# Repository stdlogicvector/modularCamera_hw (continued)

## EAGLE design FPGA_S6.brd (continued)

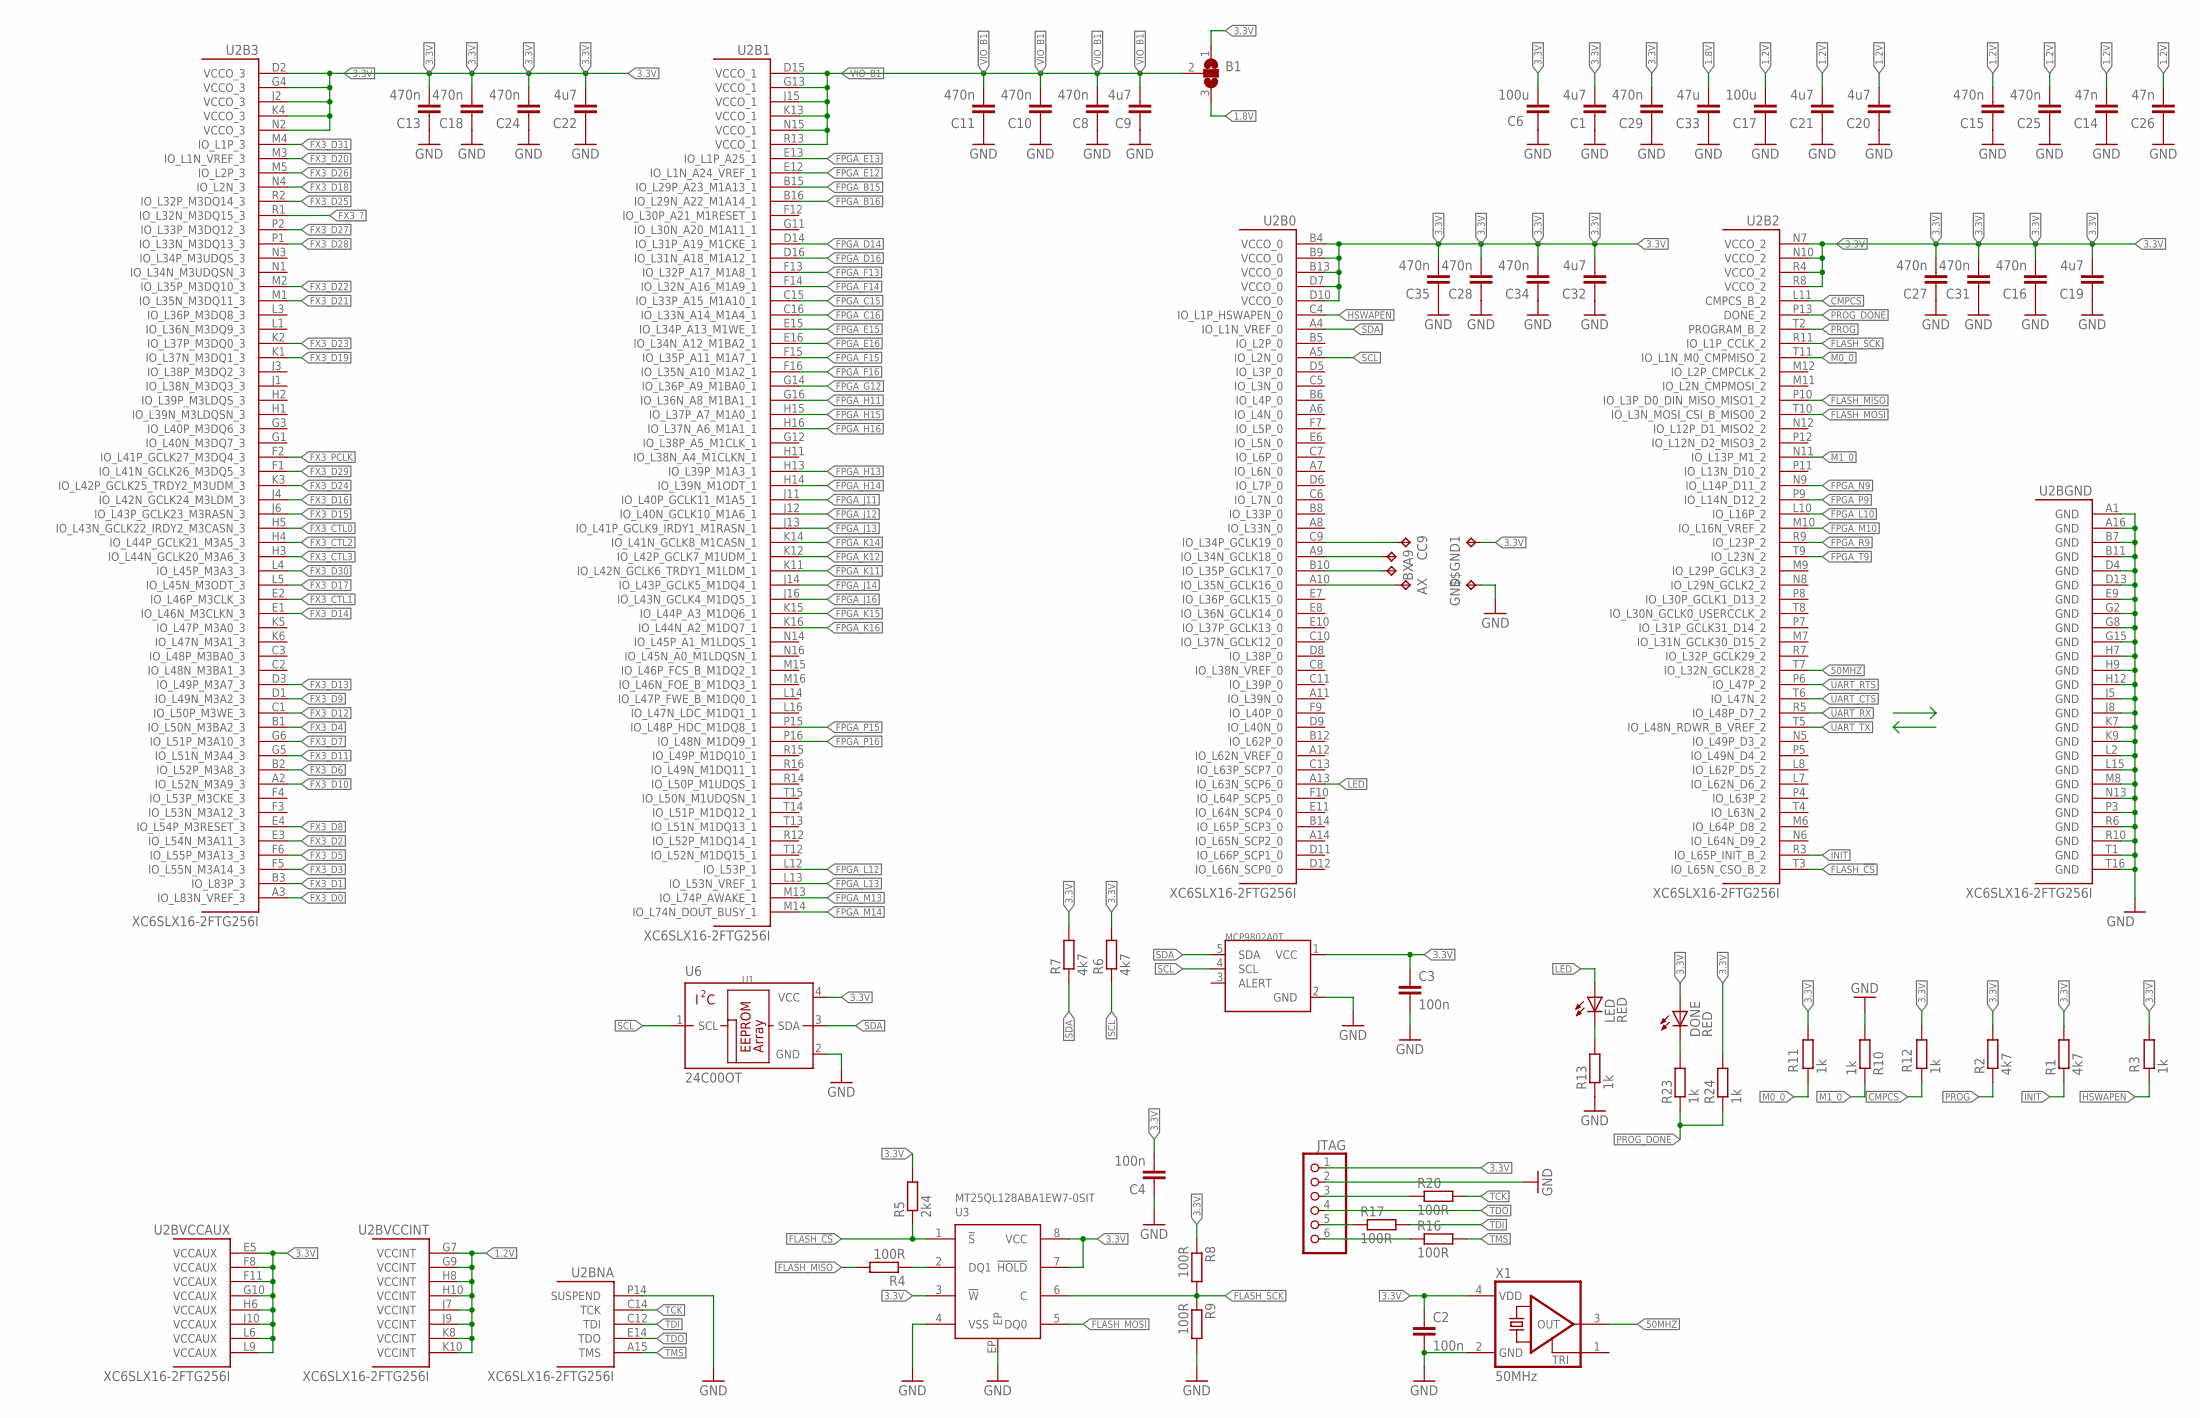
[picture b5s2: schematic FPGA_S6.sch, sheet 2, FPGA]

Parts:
$$GND1: TPTP15R; TP15R
A9: TPTP15R; TP15R
AX: TPTP15R; TP15R
B1: SJ2W; SJ_2
BX: TPTP15R; TP15R
C1, C9, C19, C20, C21, C22, C32: 4u7; C0603; LCSC C19666
C2, C3, C4: 100n; C0402; LCSC C1525
C6, C17: 100u; C1206; DIGIKEY 490-GRM31CD80J107MEA8LCT-ND
C8, C10, C11, C13, C15, C16, C18, C24, C25, C27, C28, C29, C31, C34, C35: 470n; C0402; LCSC C162159
C14, C26: 47n; C0402; LCSC C327054
C33: 47u; C0805; LCSC C77072
CC9: TPTP15R; TP15R
DONE: RED; CHIP-LED0603; LCSC C7493803
GND: TPTP15R; TP15R
JTAG: PINHD-1X6_2.00; 1X06M
LED: RED; CHIP-LED0603; LCSC C7493803
R1, R2, R6, R7: 4k7; R0402; LCSC C25900
R3, R10, R11, R12, R13, R23, R24: 1k; R0402; LCSC C11702
R4, R8, R9, R16, R17, R20: 100R; R0402; LCSC C25076
R5: 2k4; R0402
U1: MCP9802A0T; SOT23-5L; FARNELL 1439487
U2: XC6SLX16-2FTG256I; FT256; DIGIKEY 122-1752-ND
U3: MT25QL128ABA1EW7-0SIT
U6: 24C00OT; SOT23-5L
X1: 50MHz; ASE; MPN_ ASE-50.000MHZ-E-T; FARNELL 2467898

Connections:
1.2V: C14.2, C15.2, C17.1, C20.2, C21.2, C25.2, C26.2, U2.G7 (VCCINT), U2.G9 (VCCINT), U2.H8 (VCCINT), U2.H10 (VCCINT), U2.J7 (VCCINT), U2.J9 (VCCINT), U2.K8 (VCCINT), U2.K10 (VCCINT); also elsewhere on the board
1.8V: B1.3, C33.2; also elsewhere on the board
3.3V: $$GND1.TP, B1.1, C1.2, C2.1, C3.1, C4.2, C6.1, C13.2, C16.2, C18.2, C19.2, C22.2, C24.2, C27.2, C28.2, C29.2, C31.2, C32.2, C34.2, C35.2, DONE.A, JTAG.1, R1.2, R2.1, R3.1, R5.2, R6.1, R7.1, R8.1, R11.1, R12.1, R24.2, U1.1 (VCC), U2.B4 (VCCO_0), U2.B9 (VCCO_0), U2.B13 (VCCO_0), U2.D2 (VCCO_3), U2.D7 (VCCO_0), U2.D10 (VCCO_0), U2.E5 (VCCAUX), U2.F8 (VCCAUX), U2.F11 (VCCAUX), U2.G4 (VCCO_3), U2.G10 (VCCAUX), U2.H6 (VCCAUX), U2.J2 (VCCO_3), U2.J10 (VCCAUX), U2.K4 (VCCO_3), U2.L6 (VCCAUX), U2.L9 (VCCAUX), U2.N2 (VCCO_3), U2.N7 (VCCO_2), U2.N10 (VCCO_2), U2.R4 (VCCO_2), U2.R8 (VCCO_2), U3.3 (!W), U3.7 (!HOLD), U3.8 (VCC), U6.4 (VCC), X1.4 (VDD); also elsewhere on the board
50MHZ: U2.T7 (IO_L32N_GCLK28_2), X1.3 (OUT)
CMPCS: R12.2, U2.L11 (CMPCS_B_2)
FLASH_!CS: R5.1, U2.T3 (IO_L65N_CSO_B_2), U3.1 (!S)
FLASH_MISO: R4.2, U2.P10 (IO_L3P_D0_DIN_MISO_MISO1_2)
FLASH_MOSI: U2.T10 (IO_L3N_MOSI_CSI_B_MISO0_2), U3.5 (DQ0)
FLASH_SCK: R8.2, R9.1, U2.R11 (IO_L1P_CCLK_2), U3.6 (C)
FPGA_B15: U2.B15 (IO_L29P_A23_M1A13_1); also elsewhere on the board
FPGA_B16: U2.B16 (IO_L29N_A22_M1A14_1); also elsewhere on the board
FPGA_C15: U2.C15 (IO_L33P_A15_M1A10_1); also elsewhere on the board
FPGA_C16: U2.C16 (IO_L33N_A14_M1A4_1); also elsewhere on the board
FPGA_D14: U2.D14 (IO_L31P_A19_M1CKE_1); also elsewhere on the board
FPGA_D16: U2.D16 (IO_L31N_A18_M1A12_1); also elsewhere on the board
FPGA_E12: U2.E12 (IO_L1N_A24_VREF_1); also elsewhere on the board
FPGA_E13: U2.E13 (IO_L1P_A25_1); also elsewhere on the board
FPGA_E15: U2.E15 (IO_L34P_A13_M1WE_1); also elsewhere on the board
FPGA_E16: U2.E16 (IO_L34N_A12_M1BA2_1); also elsewhere on the board
FPGA_F13: U2.F13 (IO_L32P_A17_M1A8_1); also elsewhere on the board
FPGA_F14: U2.F14 (IO_L32N_A16_M1A9_1); also elsewhere on the board
FPGA_F15: U2.F15 (IO_L35P_A11_M1A7_1); also elsewhere on the board
FPGA_F16: U2.F16 (IO_L35N_A10_M1A2_1); also elsewhere on the board
FPGA_G12: U2.G14 (IO_L36P_A9_M1BA0_1); also elsewhere on the board
FPGA_H11: U2.G16 (IO_L36N_A8_M1BA1_1); also elsewhere on the board
FPGA_H13: U2.H13 (IO_L39P_M1A3_1); also elsewhere on the board
FPGA_H14: U2.H14 (IO_L39N_M1ODT_1); also elsewhere on the board
FPGA_H15: U2.H15 (IO_L37P_A7_M1A0_1); also elsewhere on the board
FPGA_H16: U2.H16 (IO_L37N_A6_M1A1_1); also elsewhere on the board
FPGA_J11: U2.J11 (IO_L40P_GCLK11_M1A5_1); also elsewhere on the board
FPGA_J12: U2.J12 (IO_L40N_GCLK10_M1A6_1); also elsewhere on the board
FPGA_J13: U2.J13 (IO_L41P_GCLK9_IRDY1_M1RASN_1); also elsewhere on the board
FPGA_J14: U2.J14 (IO_L43P_GCLK5_M1DQ4_1); also elsewhere on the board
FPGA_J16: U2.J16 (IO_L43N_GCLK4_M1DQ5_1); also elsewhere on the board
FPGA_K11: U2.K11 (IO_L42N_GCLK6_TRDY1_M1LDM_1); also elsewhere on the board
FPGA_K12: U2.K12 (IO_L42P_GCLK7_M1UDM_1); also elsewhere on the board
FPGA_K14: U2.K14 (IO_L41N_GCLK8_M1CASN_1); also elsewhere on the board
FPGA_K15: U2.K15 (IO_L44P_A3_M1DQ6_1); also elsewhere on the board
FPGA_K16: U2.K16 (IO_L44N_A2_M1DQ7_1); also elsewhere on the board
FPGA_L10: U2.L10 (IO_L16P_2); also elsewhere on the board
FPGA_L12: U2.L12 (IO_L53P_1); also elsewhere on the board
FPGA_L13: U2.L13 (IO_L53N_VREF_1); also elsewhere on the board
FPGA_M10: U2.M10 (IO_L16N_VREF_2); also elsewhere on the board
FPGA_M13: U2.M13 (IO_L74P_AWAKE_1); also elsewhere on the board
FPGA_M14: U2.M14 (IO_L74N_DOUT_BUSY_1); also elsewhere on the board
FPGA_N9: U2.N9 (IO_L14P_D11_2); also elsewhere on the board
FPGA_P9: U2.P9 (IO_L14N_D12_2); also elsewhere on the board
FPGA_P15: U2.P15 (IO_L48P_HDC_M1DQ8_1); also elsewhere on the board
FPGA_P16: U2.P16 (IO_L48N_M1DQ9_1); also elsewhere on the board
FPGA_R9: U2.R9 (IO_L23P_2); also elsewhere on the board
FPGA_T9: U2.T9 (IO_L23N_2); also elsewhere on the board
FX3_?: U2.R1 (IO_L32N_M3DQ15_3); also elsewhere on the board
FX3_CTL0: U2.H5 (IO_L43N_GCLK22_IRDY2_M3CASN_3); also elsewhere on the board
FX3_CTL1: U2.E2 (IO_L46P_M3CLK_3); also elsewhere on the board
FX3_CTL2: U2.H4 (IO_L44P_GCLK21_M3A5_3); also elsewhere on the board
FX3_CTL3: U2.H3 (IO_L44N_GCLK20_M3A6_3); also elsewhere on the board
FX3_D0: U2.A3 (IO_L83N_VREF_3); also elsewhere on the board
FX3_D1: U2.B3 (IO_L83P_3); also elsewhere on the board
FX3_D2: U2.E3 (IO_L54N_M3A11_3); also elsewhere on the board
FX3_D3: U2.F5 (IO_L55N_M3A14_3); also elsewhere on the board
FX3_D4: U2.B1 (IO_L50N_M3BA2_3); also elsewhere on the board
FX3_D5: U2.F6 (IO_L55P_M3A13_3); also elsewhere on the board
FX3_D6: U2.B2 (IO_L52P_M3A8_3); also elsewhere on the board
FX3_D7: U2.G6 (IO_L51P_M3A10_3); also elsewhere on the board
FX3_D8: U2.E4 (IO_L54P_M3RESET_3); also elsewhere on the board
FX3_D9: U2.D1 (IO_L49N_M3A2_3); also elsewhere on the board
FX3_D10: U2.A2 (IO_L52N_M3A9_3); also elsewhere on the board
FX3_D11: U2.G5 (IO_L51N_M3A4_3); also elsewhere on the board
FX3_D12: U2.C1 (IO_L50P_M3WE_3); also elsewhere on the board
FX3_D13: U2.D3 (IO_L49P_M3A7_3); also elsewhere on the board
FX3_D14: U2.E1 (IO_L46N_M3CLKN_3); also elsewhere on the board
FX3_D15: U2.J6 (IO_L43P_GCLK23_M3RASN_3); also elsewhere on the board
FX3_D16: U2.J4 (IO_L42N_GCLK24_M3LDM_3); also elsewhere on the board
FX3_D17: U2.L5 (IO_L45N_M3ODT_3); also elsewhere on the board
FX3_D18: U2.N4 (IO_L2N_3); also elsewhere on the board
FX3_D19: U2.K1 (IO_L37N_M3DQ1_3); also elsewhere on the board
FX3_D20: U2.M3 (IO_L1N_VREF_3); also elsewhere on the board
FX3_D21: U2.M1 (IO_L35N_M3DQ11_3); also elsewhere on the board
FX3_D22: U2.M2 (IO_L35P_M3DQ10_3); also elsewhere on the board
FX3_D23: U2.K2 (IO_L37P_M3DQ0_3); also elsewhere on the board
FX3_D24: U2.K3 (IO_L42P_GCLK25_TRDY2_M3UDM_3); also elsewhere on the board
FX3_D25: U2.R2 (IO_L32P_M3DQ14_3); also elsewhere on the board
FX3_D26: U2.M5 (IO_L2P_3); also elsewhere on the board
FX3_D27: U2.P2 (IO_L33P_M3DQ12_3); also elsewhere on the board
FX3_D28: U2.P1 (IO_L33N_M3DQ13_3); also elsewhere on the board
FX3_D29: U2.F1 (IO_L41N_GCLK26_M3DQ5_3); also elsewhere on the board
FX3_D30: U2.L4 (IO_L45P_M3A3_3); also elsewhere on the board
FX3_D31: U2.M4 (IO_L1P_3); also elsewhere on the board
FX3_PCLK: U2.F2 (IO_L41P_GCLK27_M3DQ4_3); also elsewhere on the board
GND: C1.1, C2.2, C3.2, C4.1, C6.2, C8.1, C9.1, C10.1, C11.1, C13.1, C14.1, C15.1, C16.1, C17.2, C18.1, C19.1, C20.1, C21.1, C22.1, C24.1, C25.1, C26.1, C27.1, C28.1, C29.1, C31.1, C32.1, C33.1, C34.1, C35.1, GND.TP, JTAG.2, R9.2, R10.2, R13.1, U1.2 (GND), U2.A1 (GND), U2.A16 (GND), U2.B7 (GND), U2.B11 (GND), U2.D4 (GND), U2.D13 (GND), U2.E9 (GND), U2.G2 (GND), U2.G8 (GND), U2.G15 (GND), U2.H7 (GND), U2.H9 (GND), U2.H12 (GND), U2.J5 (GND), U2.J8 (GND), U2.K7 (GND), U2.K9 (GND), U2.L2 (GND), U2.L15 (GND), U2.M8 (GND), U2.N13 (GND), U2.P3 (GND), U2.P14 (SUSPEND), U2.R6 (GND), U2.R10 (GND), U2.T1 (GND), U2.T16 (GND), U3.4 (VSS), U3.EP, U6.2 (GND), X1.2 (GND); also elsewhere on the board
HSWAPEN: R3.2, U2.C4 (IO_L1P_HSWAPEN_0)
INIT: R1.1, U2.R3 (IO_L65P_INIT_B_2)
LED: LED.A, U2.A13 (IO_L63N_SCP6_0)
M0_0: R11.2, U2.T11 (IO_L1N_M0_CMPMISO_2)
M1_0: R10.1, U2.N11 (IO_L13P_M1_2)
unnamed: BX.TP, U2.B10 (IO_L35P_GCLK17_0)
unnamed: LED.C, R13.2
unnamed: R4.1, U3.2 (DQ1)
unnamed: AX.TP, U2.A10 (IO_L35N_GCLK16_0)
unnamed: A9.TP, U2.A9 (IO_L34N_GCLK18_0)
unnamed: CC9.TP, U2.C9 (IO_L34P_GCLK19_0)
unnamed: DONE.C, R23.2
unnamed: JTAG.5, R17.1
unnamed: JTAG.3, R20.1
unnamed: JTAG.6, R16.1
PROG: R2.2, U2.T2 (PROGRAM_B_2)
PROG_DONE: R23.1, R24.1, U2.P13 (DONE_2)
SCL: R6.2, U1.4 (SCL), U2.A5 (IO_L2N_0), U6.1 (SCL)
SDA: R7.2, U1.5 (SDA), U2.A4 (IO_L1N_VREF_0), U6.3 (SDA)
TCK: R20.2, U2.C14 (TCK)
TDI: R17.2, U2.C12 (TDI)
TDO: JTAG.4, U2.E14 (TDO)
TMS: R16.2, U2.A15 (TMS)
UART_CTS: U2.T6 (IO_L47N_2); also elsewhere on the board
UART_RTS: U2.P6 (IO_L47P_2); also elsewhere on the board
UART_RX: U2.R5 (IO_L48P_D7_2); also elsewhere on the board
UART_TX: U2.T5 (IO_L48N_RDWR_B_VREF_2); also elsewhere on the board
VIO_B1: B1.2, C8.2, C9.2, C10.2, C11.2, U2.D15 (VCCO_1), U2.G13 (VCCO_1), U2.J15 (VCCO_1), U2.K13 (VCCO_1), U2.N15 (VCCO_1), U2.R13 (VCCO_1)

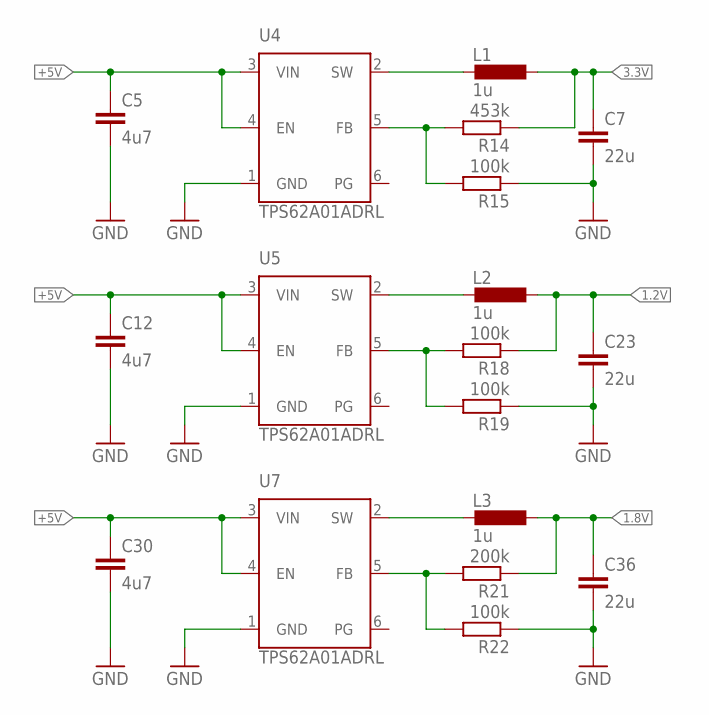
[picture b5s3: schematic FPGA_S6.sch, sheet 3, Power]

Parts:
C5, C12, C30: 4u7; C0603; LCSC C19666
C7, C23, C36: 22u; C0603; LCSC C109448
L1, L2, L3: 1u; L1008; MPN LQM2HPN1R0MG0L; DIGIKEY 490-5112-1-ND
R14: 453k; R0402; LCSC C137978
R15: 100k; R0402; DIGIKEY RMCF0402FT100KCT-ND
R18: 100k; R0402; DIGIKEY RMCF0402FT66K5CT-ND
R19, R22: 100k; R0402; LCSC C60491
R21: 200k; R0402; LCSC C114763
U4, U5, U7: TPS62A01ADRL; SOTFL50P160X60-6N; DIGIKEY 296-TPS62A01ADRLRCT-ND

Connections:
1.2V: C23.1, L2.1, R18.1; also elsewhere on the board
1.8V: C36.1, L3.1, R21.1; also elsewhere on the board
3.3V: C7.1, L1.1, R14.1; also elsewhere on the board
+5V: C5.1, C12.1, C30.1, U4.3 (VIN), U4.4 (EN), U5.3 (VIN), U5.4 (EN), U7.3 (VIN), U7.4 (EN); also elsewhere on the board
GND: C5.2, C7.2, C12.2, C23.2, C30.2, C36.2, R15.1, R19.1, R22.1, U4.1 (GND), U5.1 (GND), U7.1 (GND); also elsewhere on the board
unnamed: L2.2, U5.2 (SW)
unnamed: R18.2, R19.2, U5.5 (FB)
unnamed: R14.2, R15.2, U4.5 (FB)
unnamed: L3.2, U7.2 (SW)
unnamed: R21.2, R22.2, U7.5 (FB)
unnamed: L1.2, U4.2 (SW)

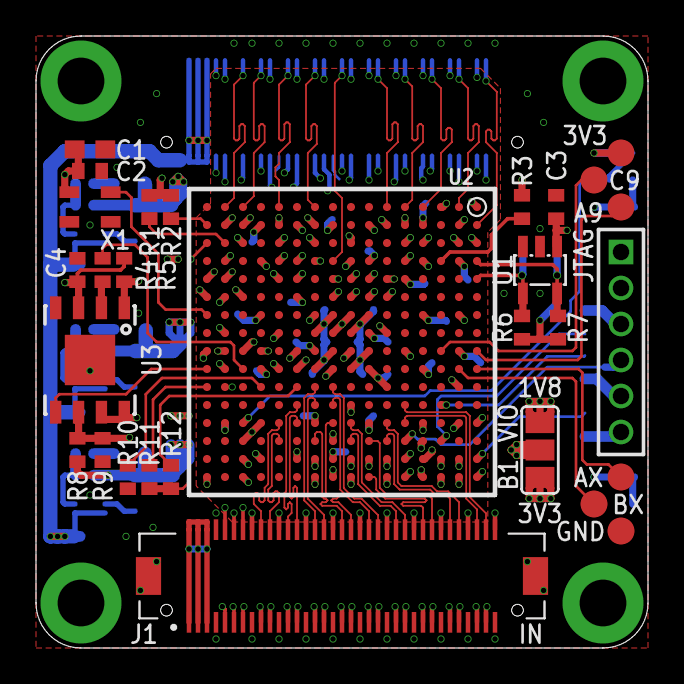
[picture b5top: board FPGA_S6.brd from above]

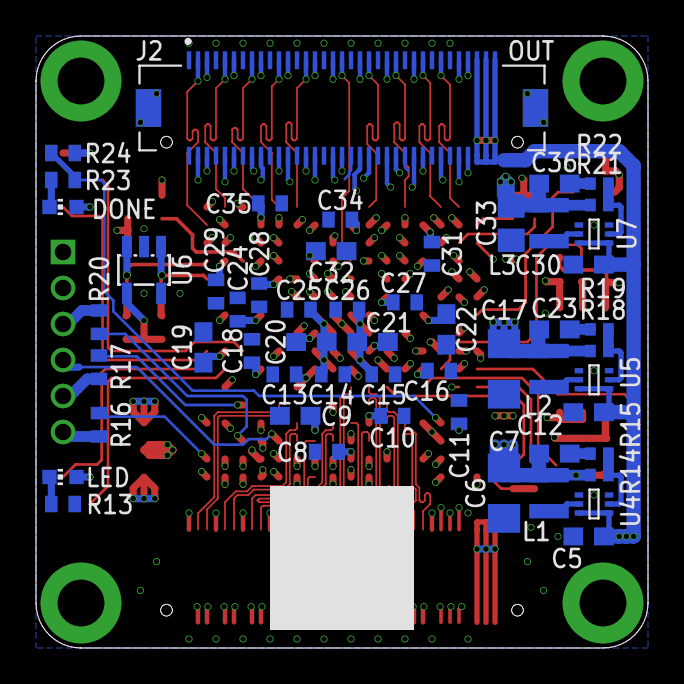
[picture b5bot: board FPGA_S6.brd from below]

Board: 6 copper layers, 34.0 x 34.0 mm, 83 parts (54 on the bottom side), 125 nets.

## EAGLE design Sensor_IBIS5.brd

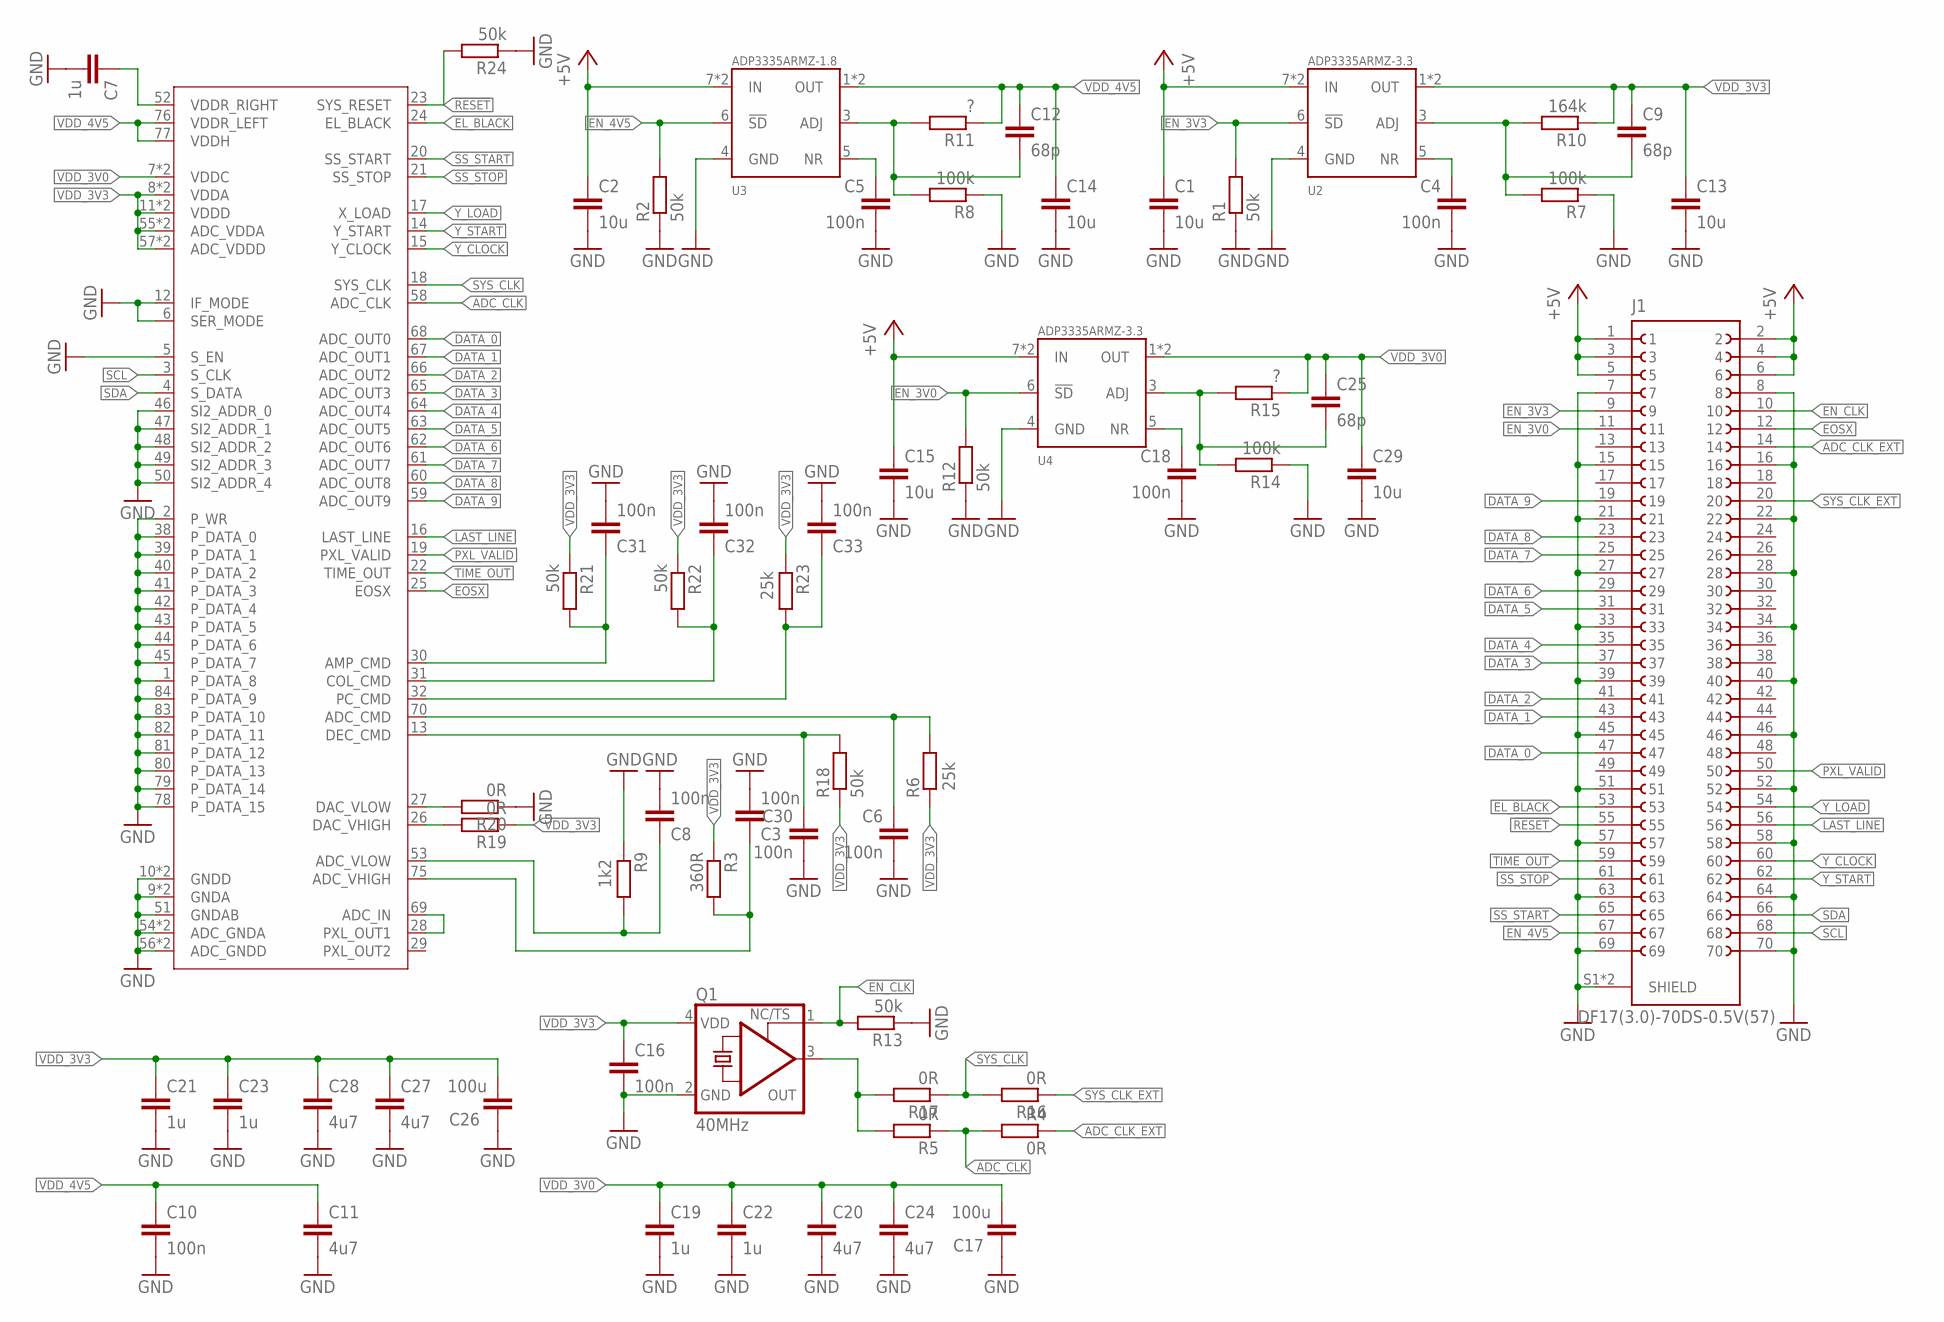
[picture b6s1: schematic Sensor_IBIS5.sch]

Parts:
C1, C2, C13, C14, C15, C29: 10u; C0603
C3, C4, C5, C6, C8, C10, C16, C18, C30, C31, C32, C33: 100n; C0402; LCSC C1525
C7, C19, C21, C22, C23: 1u; C0402
C9, C12, C25: 68p; C0402; LCSC C1525
C11, C20, C24, C27, C28: 4u7; C0603; LCSC C19666
C17, C26: 100u; C1206; DIGIKEY 490-GRM31CD80J107MEA8LCT-ND
J1: DF17(3.0)-70DS-0.5V(57)
Q1: 40MHz; 3.2X2.5_KXO-V96; DIGIKEY 1473-SIT8208AC-23-33E-72.000000-ND
R1, R2, R12, R13, R18, R21, R22, R24: 50k; R0402
R3: 360R; R0402
R4, R5, R16, R17, R19, R20: 0R; R0402
R6, R23: 25k; R0402
R7, R8, R14: 100k; R0402
R9: 1k2; R0402
R10: 164k; R0402
R11, R15: ?; R0402
U1: CYII5FM1300AB; LCC-84
U2, U4: ADP3335ARMZ-3.3; MSOP08; DIGIKEY 505-ADP3335ARMZ-3.3RL7CT-ND
U3: ADP3335ARMZ-1.8; MSOP08; DIGIKEY 505-ADP3335ARMZ-1.8-R7CT-ND

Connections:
!RESET: J1.55, R24.2, U1.23 (SYS_RESET)
+5V: C1.1, C2.1, C15.1, J1.1, J1.2, J1.3, J1.4, J1.5, J1.6, U2.7 (IN), U2.8 (IN), U3.7 (IN), U3.8 (IN), U4.7 (IN), U4.8 (IN)
ADC_CLK: R4.2, R5.1, U1.58 (ADC_CLK)
ADC_CLK_EXT: J1.14, R4.1
CLK: Q1.3 (OUT), R5.2, R17.2
DATA_0: J1.47, U1.68 (ADC_OUT0)
DATA_1: J1.43, U1.67 (ADC_OUT1)
DATA_2: J1.41, U1.66 (ADC_OUT2)
DATA_3: J1.37, U1.65 (ADC_OUT3)
DATA_4: J1.35, U1.64 (ADC_OUT4)
DATA_5: J1.31, U1.63 (ADC_OUT5)
DATA_6: J1.29, U1.62 (ADC_OUT6)
DATA_7: J1.25, U1.61 (ADC_OUT7)
DATA_8: J1.23, U1.60 (ADC_OUT8)
DATA_9: J1.19, U1.59 (ADC_OUT9)
EL_BLACK: J1.53, U1.24 (EL_BLACK)
EN_3V0: J1.11, R12.2, U4.6 (!SD)
EN_3V3: J1.9, R1.2, U2.6 (!SD)
EN_4V5: J1.67, R2.2, U3.6 (!SD)
EN_CLK: J1.10, Q1.1 (TS), R13.2
EOSX: J1.12, U1.25 (EOSX)
GND: C1.2, C2.2, C3.2, C4.2, C5.2, C6.2, C7.2, C8.2, C10.2, C11.2, C13.2, C14.2, C15.2, C16.2, C17.2, C18.2, C19.2, C20.2, C21.2, C22.2, C23.2, C24.2, C26.2, C27.2, C28.2, C29.2, C30.2, C31.2, C32.2, C33.2, J1.7, J1.8, J1.15, J1.16, J1.21, J1.22, J1.27, J1.28, J1.33, J1.34, J1.39, J1.40, J1.45, J1.46, J1.51, J1.52, J1.57, J1.58, J1.63, J1.64, J1.69, J1.70, J1.S1 (SHIELD), J1.S2 (SHIELD), Q1.2 (GND), R1.1, R2.1, R7.1, R8.1, R9.1, R12.1, R13.1, R14.1, R20.1, R24.1, U1.1 (P_DATA_8), U1.2 (P_WR), U1.5 (S_EN), U1.6 (SER_MODE), U1.9 (GNDA), U1.10 (GNDD), U1.12 (IF_MODE), U1.34 (GNDD), U1.35 (GNDA), U1.38 (P_DATA_0), U1.39 (P_DATA_1), U1.40 (P_DATA_2), U1.41 (P_DATA_3), U1.42 (P_DATA_4), U1.43 (P_DATA_5), U1.44 (P_DATA_6), U1.45 (P_DATA_7), U1.46 (SI2_ADDR_0), U1.47 (SI2_ADDR_1), U1.48 (SI2_ADDR_2), U1.49 (SI2_ADDR_3), U1.50 (SI2_ADDR_4), U1.51 (GNDAB), U1.54 (ADC_GNDA), U1.56 (ADC_GNDD), U1.72 (ADC_GNDA), U1.73 (ADC_GNDD), U1.78 (P_DATA_15), U1.79 (P_DATA_14), U1.80 (P_DATA_13), U1.81 (P_DATA_12), U1.82 (P_DATA_11), U1.83 (P_DATA_10), U1.84 (P_DATA_9), U2.4 (GND), U3.4 (GND), U4.4 (GND)
LAST_LINE: J1.56, U1.16 (LAST_LINE)
unnamed: U1.28 (PXL_OUT1), U1.69 (ADC_IN)
unnamed: C18.1, U4.5 (NR)
unnamed: C5.1, U3.5 (NR)
unnamed: C4.1, U2.5 (NR)
unnamed: R19.2, U1.26 (DAC_VHIGH)
unnamed: R20.2, U1.27 (DAC_VLOW)
unnamed: C30.1, R18.2, U1.13 (DEC_CMD)
unnamed: C32.1, R22.2, U1.31 (COL_CMD)
unnamed: C33.1, R23.2, U1.32 (PC_CMD)
unnamed: C31.1, R21.2, U1.30 (AMP_CMD)
unnamed: C6.1, R6.2, U1.70 (ADC_CMD)
unnamed: C3.1, R3.2, U1.75 (ADC_VHIGH)
unnamed: C8.1, R9.2, U1.53 (ADC_VLOW)
unnamed: C7.1, U1.52 (VDDR_RIGHT)
unnamed: C12.2, R8.2, R11.2, U3.3 (ADJ)
unnamed: C9.2, R7.2, R10.2, U2.3 (ADJ)
unnamed: C25.2, R14.2, R15.2, U4.3 (ADJ)
PXL_VALID: J1.50, U1.19 (PXL_VALID)
SCL: J1.68, U1.3 (S_CLK)
SDA: J1.66, U1.4 (S_DATA)
SS_START: J1.65, U1.20 (SS_START)
SS_STOP: J1.61, U1.21 (SS_STOP)
SYS_CLK: R16.2, R17.1, U1.18 (SYS_CLK)
SYS_CLK_EXT: J1.20, R16.1
TIME_OUT: J1.59, U1.22 (TIME_OUT)
VDD_3V0: C17.1, C19.1, C20.1, C22.1, C24.1, C25.1, C29.1, R15.1, U1.7 (VDDC), U1.37 (VDDC), U4.1 (OUT), U4.2 (OUT)
VDD_3V3: C9.1, C13.1, C16.1, C21.1, C23.1, C26.1, C27.1, C28.1, Q1.4 (VDD), R3.1, R6.1, R10.1, R18.1, R19.1, R21.1, R22.1, R23.1, U1.8 (VDDA), U1.11 (VDDD), U1.33 (VDDD), U1.36 (VDDA), U1.55 (ADC_VDDA), U1.57 (ADC_VDDD), U1.71 (ADC_VDDD), U1.74 (ADC_VDDA), U2.1 (OUT), U2.2 (OUT)
VDD_4V5: C10.1, C11.1, C12.1, C14.1, R11.1, U1.76 (VDDR_LEFT), U1.77 (VDDH), U3.1 (OUT), U3.2 (OUT)
Y_CLOCK: J1.60, U1.15 (Y_CLOCK)
Y_LOAD: J1.54, U1.17 (X_LOAD)
Y_START: J1.62, U1.14 (Y_START)

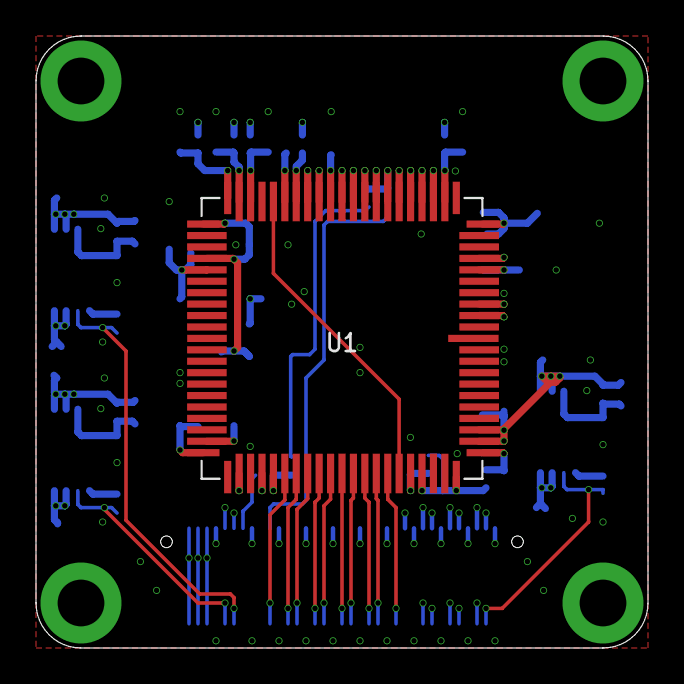
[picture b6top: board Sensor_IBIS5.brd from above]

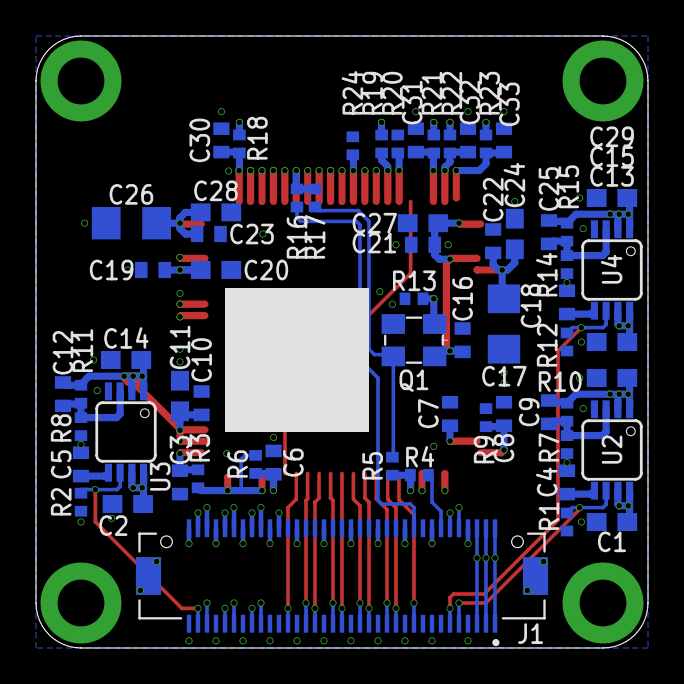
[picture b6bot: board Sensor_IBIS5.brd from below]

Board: 4 copper layers, 34.0 x 34.0 mm, 63 parts (62 on the bottom side), 54 nets.
